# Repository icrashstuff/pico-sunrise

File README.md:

# pico-sunrise
A sunrise clock for RP2040 based microcontrollers

## Parts
- RP2040 based microcontroller (Raspberry Pi Pico) - Such as https://www.adafruit.com/product/4883
- PA1616S GPS Module - MTK3339 Chipset - Such as https://www.adafruit.com/product/746
- SK6812RGBW individually addressable LED strip - Such as https://www.adafruit.com/product/4913

## Configuration
[config.h](config.h)

## License (pico-sunrise)
Copyright (c) 2025 Ian Hangartner <icrashstuff at outlook dot com>

Permission is hereby granted, free of charge, to any person obtaining a
copy of this software and associated documentation files (the "Software"),
to deal in the Software without restriction, including without limitation
the rights to use, copy, modify, merge, publish, distribute, sublicense,
and/or sell copies of the Software, and to permit persons to whom the
Software is furnished to do so, subject to the following conditions:

The above copyright notice and this permission notice shall be included in
all copies or substantial portions of the Software.

THE SOFTWARE IS PROVIDED "AS IS", WITHOUT WARRANTY OF ANY KIND, EXPRESS OR
IMPLIED, INCLUDING BUT NOT LIMITED TO THE WARRANTIES OF MERCHANTABILITY,
FITNESS FOR A PARTICULAR PURPOSE AND NONINFRINGEMENT. IN NO EVENT SHALL THE
AUTHORS OR COPYRIGHT HOLDERS BE LIABLE FOR ANY CLAIM, DAMAGES OR OTHER
LIABILITY, WHETHER IN AN ACTION OF CONTRACT, TORT OR OTHERWISE, ARISING
FROM, OUT OF OR IN CONNECTION WITH THE SOFTWARE OR THE USE OR OTHER
DEALINGS IN THE SOFTWARE.

## License (pico-sdk and pico-examples)
Copyright 2020-2025 (c) 2020-2025 Raspberry Pi (Trading) Ltd.

Redistribution and use in source and binary forms, with or without modification, are permitted provided that the
following conditions are met:

1. Redistributions of source code must retain the above copyright notice, this list of conditions and the following
disclaimer.

2. Redistributions in binary form must reproduce the above copyright notice, this list of conditions and the following
disclaimer in the documentation and/or other materials provided with the distribution.

3. Neither the name of the copyright holder nor the names of its contributors may be used to endorse or promote products
derived from this software without specific prior written permission.

THIS SOFTWARE IS PROVIDED BY THE COPYRIGHT HOLDERS AND CONTRIBUTORS "AS IS" AND ANY EXPRESS OR IMPLIED WARRANTIES,
INCLUDING, BUT NOT LIMITED TO, THE IMPLIED WARRANTIES OF MERCHANTABILITY AND FITNESS FOR A PARTICULAR PURPOSE ARE
DISCLAIMED. IN NO EVENT SHALL THE COPYRIGHT HOLDER OR CONTRIBUTORS BE LIABLE FOR ANY DIRECT, INDIRECT, INCIDENTAL,
SPECIAL, EXEMPLARY, OR CONSEQUENTIAL DAMAGES (INCLUDING, BUT NOT LIMITED TO, PROCUREMENT OF SUBSTITUTE GOODS OR
SERVICES; LOSS OF USE, DATA, OR PROFITS; OR BUSINESS INTERRUPTION) HOWEVER CAUSED AND ON ANY THEORY OF LIABILITY,
WHETHER IN CONTRACT, STRICT LIABILITY, OR TORT (INCLUDING NEGLIGENCE OR OTHERWISE) ARISING IN ANY WAY OUT OF THE USE OF
THIS SOFTWARE, EVEN IF ADVISED OF THE POSSIBILITY OF SUCH DAMAGE.

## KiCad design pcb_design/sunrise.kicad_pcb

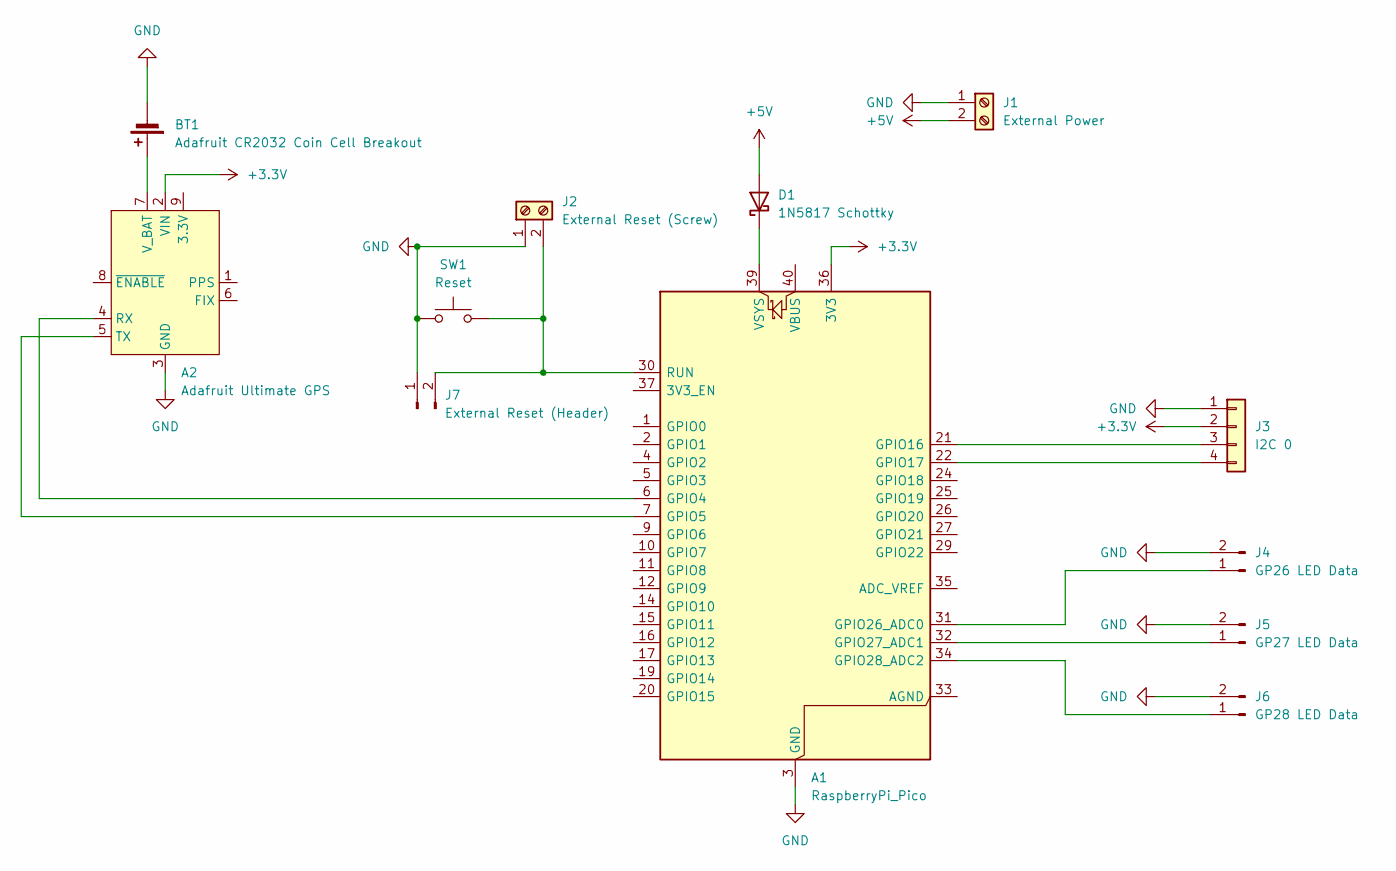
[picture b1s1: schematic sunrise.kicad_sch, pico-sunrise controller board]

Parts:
A1: RaspberryPi_Pico; RaspberryPi_Pico_Common_THT
A2: Adafruit Ultimate GPS; Adafruit_Ultimate_GPS_Breakout
BT1: Adafruit CR2032 Coin Cell Breakout; Adfruit_CR2032_Breakout
D1: 1N5817 Schottky; D_DO-41_SOD81_P10.16mm_Horizontal
J1: External Power; TerminalBlock_MetzConnect_Type101_RT01602HBWC_1x02_P5.08mm_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
J2: External Reset (Screw); TerminalBlock_MetzConnect_Type101_RT01602HBWC_1x02_P5.08mm_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
J3: I2C 0; PinHeader_1x04_P2.54mm_Vertical
J4: GP26 LED Data; PinHeader_1x02_P2.54mm_Vertical
J5: GP27 LED Data; PinHeader_1x02_P2.54mm_Vertical
J6: GP28 LED Data; PinHeader_1x02_P2.54mm_Vertical
J7: External Reset (Header); PinHeader_1x02_P2.54mm_Vertical
SW1: Reset; SW_TH_Tactile_Omron_B3F-100x

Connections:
+3.3V: A1.36 (3V3), A2.2 (VIN), J3.2
+5V: D1.2 (A), J1.2
GND: A1.3 (GND), A1.8 (GND), A1.13 (GND), A1.18 (GND), A1.23 (GND), A1.28 (GND), A1.38 (GND), A2.3 (GND), BT1.2 (-), J1.1, J2.1, J3.1, J4.2, J5.2, J6.2, J7.1, SW1.1
unnamed: A1.6 (GPIO4), A2.4 (RX)
unnamed: A1.7 (GPIO5), A2.5 (TX)
unnamed: A1.21 (GPIO16), J3.3
unnamed: A1.22 (GPIO17), J3.4
unnamed: A1.31 (GPIO26_ADC0), J4.1
unnamed: A1.32 (GPIO27_ADC1), J5.1
unnamed: A1.34 (GPIO28_ADC2), J6.1
unnamed: A1.30 (RUN), J2.2, J7.2, SW1.2
unnamed: A1.39 (VSYS), D1.1 (K)
unnamed: A2.7 (V_BAT), BT1.1 (+)

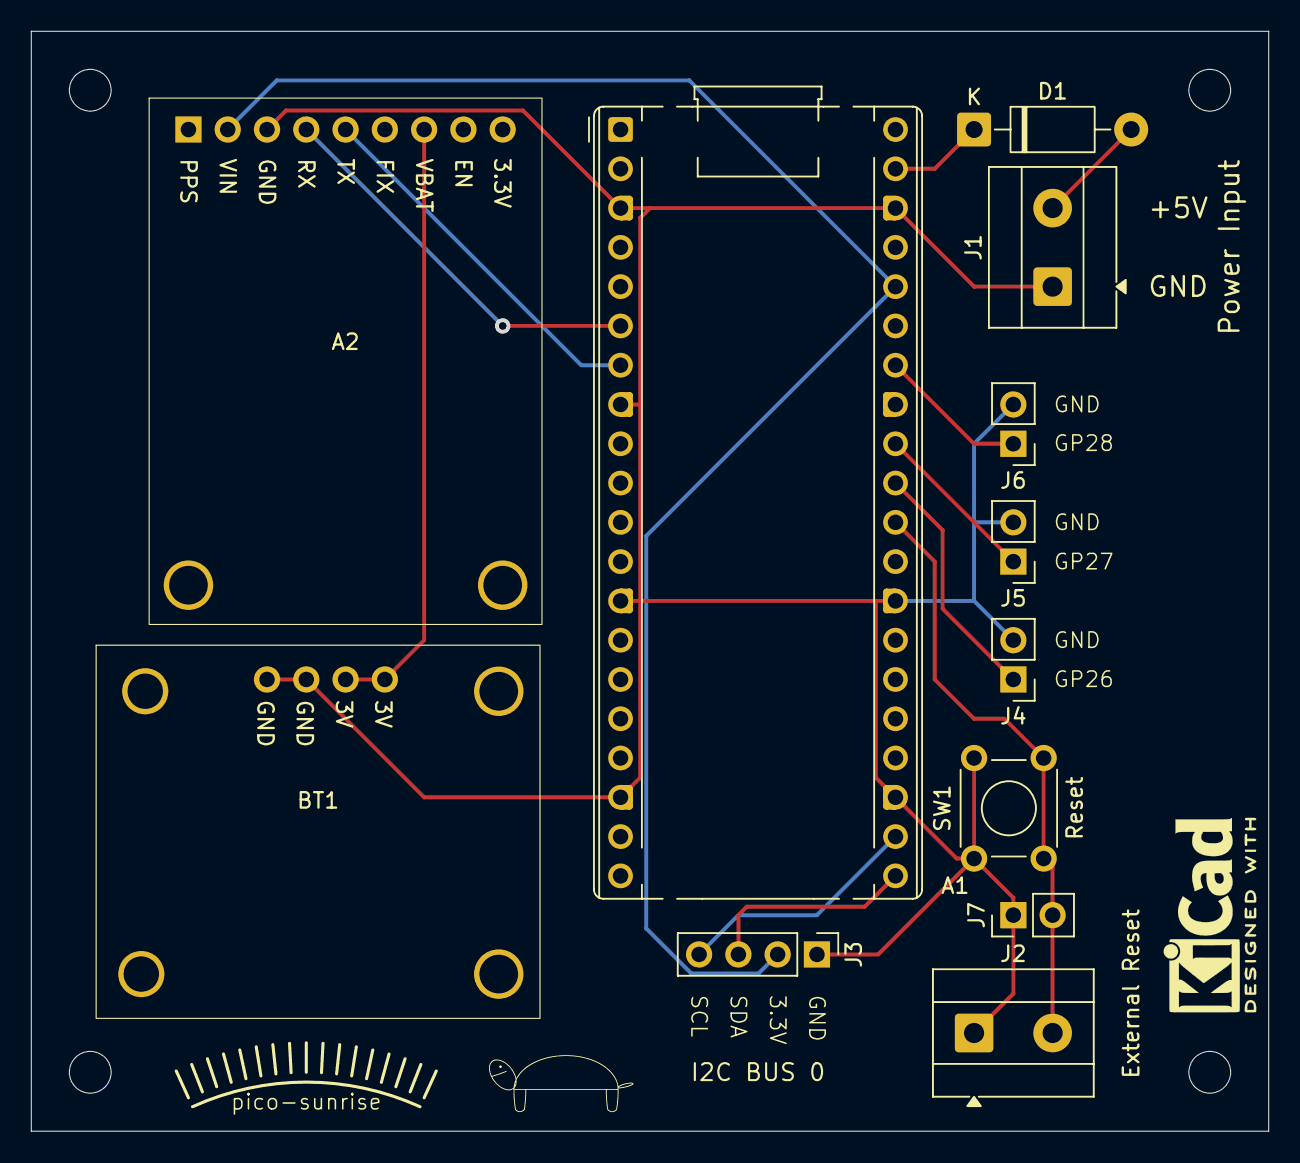
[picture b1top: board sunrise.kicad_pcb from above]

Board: 2 copper layers, 80.0 x 71.1 mm, 13 parts (0 on the bottom side), 13 nets.

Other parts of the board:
SYM_KICAD: KiCad-Logo2_5mm_SilkScreen

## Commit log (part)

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2025-12-13 Remove hard-coded serial number from upload script
2025-12-13 Add clang-format and pre-commit config files
2025-12-13 Add some functions related to using the default timer as a realtime clock
2025-12-14 Switch to C++ and add datetime handling structures
    - Added simple DST/Timezone correction
    - Datetime handling structures were inspired by Adafruit's RTClib, but the implementation is mine
2025-12-14 Sync file comment from datetime.h -> datetime.cpp
2025-12-14 Add doxygen config and revise file comments
2025-12-14 Add GPS time synchronization
2025-12-14 Add -Wshadow to compile flags
2025-12-14 Add interface to get and set unix time without disturbing the hardware clock
2025-12-14 Move license text strings to a separate header file
2025-12-14 Add bug note about GPS functions potentially dropping some packets
2025-12-14 Reduce frequency of gps_set_config() calls to 0.2Hz
2025-12-14 Decouple status frequency from main loop frequency
2025-12-14 Fix lack of format string checking for status()
2025-12-14 Add structure to measure loop performance
2025-12-15 Add interface for WS2812 style leds
    - ws2812.pio from pico-examples does the heavy lifting
2025-12-15 Use heap instead of stack for buf in gps_write_nmea()
2025-12-16 Fix gps_write_nmea() not using full buffer
2025-12-16 Add sunrise simulation
2025-12-16 Suppress unused argument warnings caused by status_impl_dummy_func()
2025-12-16 Force C/C++ standards
2025-12-16 Add README
2025-12-17 Actually fix lack of format string checking for status()
2025-12-17 Correct minor error in pico-sdk/pico-examples license
2025-12-17 Fix (Or at least reduce) bug in gps_write_nmea() that causes some data from the GPS module to be lost
2025-12-18 Add watchdog for both cores
2025-12-20 Switch from only using sscanf(3) to extract data from NMEA packets to an argv like approach
2025-12-20 Remove extraneous line added by previous commit
2025-12-31 Add electrical schematic and PCB design
2026-01-18 Adjust LED_GPIO for PCB design
2026-01-19 Raise default LED_FREQUENCY (800kHZ -> 1100kHZ)
2026-01-19 Add dithering of led brightness
    - I not certain if what I have written is actually dithering, but it achieves
    my goal of masking quantization errors, so I'm not going to question it
2026-01-19 Remove 1ms sleep from core 0 loop
2026-01-19 Determine dither loop step count at runtime for a configurable target frequency
2026-01-24 Lower default LED_FREQUENCY (1100kHz ->1000kHz)
2026-01-25 Mix between top and bottom color temperatures instead of top and bottom color
